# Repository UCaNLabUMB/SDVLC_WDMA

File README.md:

# SDVLC_WDMA
Board files and test software for an optical wireless communications wavelength division multiple access (WDMA) transmitter with compatibility for USRP software defined radio hardware.

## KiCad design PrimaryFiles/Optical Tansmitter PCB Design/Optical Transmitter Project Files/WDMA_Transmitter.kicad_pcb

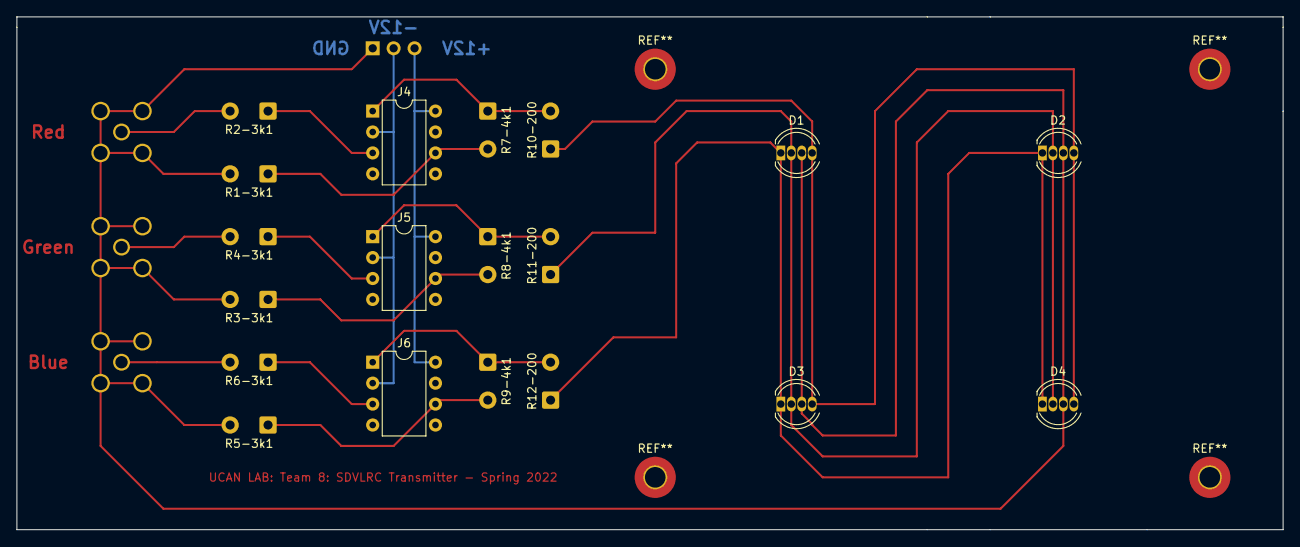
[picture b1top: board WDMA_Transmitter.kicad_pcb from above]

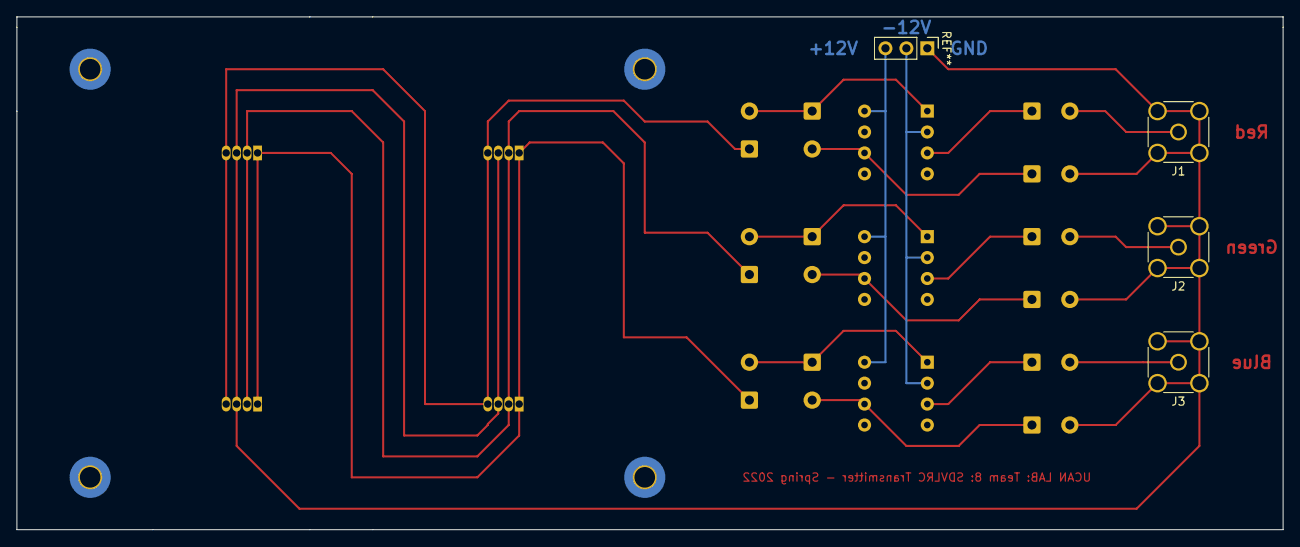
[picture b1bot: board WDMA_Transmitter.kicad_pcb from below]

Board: 2 copper layers, 153.7 x 62.2 mm, 22 parts (3 on the bottom side), 18 nets.

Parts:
D1, D2, D3, D4: LED_BGAR; LED_D5.0mm-4_RGB
J1, J2, J3: Conn_Coaxial; SMA_Wurth_60312002114503_Vertical
J4, J5, J6: Conn_02x04_Counter_Clockwise; DIP-8_W7.62mm
R1-3k1, R2-3k1, R3-3k1, R4-3k1, R5-3k1, R6-3k1: 3k; SolderWire-0.5sqmm_1x02_P4.6mm_D0.9mm_OD2.1mm
R7-4k1, R8-4k1, R9-4k1: 4k; SolderWire-0.5sqmm_1x02_P4.6mm_D0.9mm_OD2.1mm
R10-200, R11-200, R12-200: 200; SolderWire-0.5sqmm_1x02_P4.6mm_D0.9mm_OD2.1mm

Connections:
+12V: J4.8, J5.8, J6.8
-12V: J4.2, J5.2, J6.2
GND: D1.3, D2.3, D3.3, D4.3, J1.2, J2.2, J3.2, R1-3k1.2, R3-3k1.2, R5-3k1.2
unnamed: D1.1, D2.1, D3.1, D4.1, R12-200.1
unnamed: D1.2, D2.2, D3.2, D4.2, R11-200.1
unnamed: D1.4, D2.4, D3.4, D4.4, R10-200.1
unnamed: J1.1, R2-3k1.2
unnamed: J2.1, R4-3k1.2
unnamed: J3.1, R6-3k1.2
unnamed: J4.1, R7-4k1.1, R10-200.2
unnamed: J4.3, R2-3k1.1
unnamed: J4.6, R1-3k1.1, R7-4k1.2
unnamed: J5.1, R8-4k1.1, R11-200.2
unnamed: J5.3, R4-3k1.1
unnamed: J5.6, R3-3k1.1, R8-4k1.2
unnamed: J6.1, R9-4k1.1, R12-200.2
unnamed: J6.3, R6-3k1.1
unnamed: J6.6, R5-3k1.1, R9-4k1.2

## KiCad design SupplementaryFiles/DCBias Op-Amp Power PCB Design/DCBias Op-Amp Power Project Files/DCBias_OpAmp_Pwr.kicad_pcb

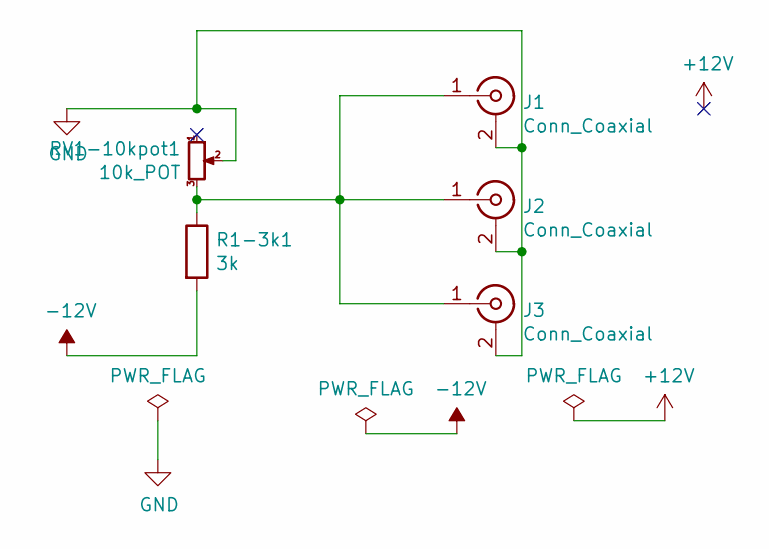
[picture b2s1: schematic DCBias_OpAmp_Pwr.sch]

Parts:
J1, J2, J3: Conn_Coaxial; SMA_Wurth_60312002114503_Vertical
R1-3k1: 3k; SolderWire-0.5sqmm_1x02_P4.6mm_D0.9mm_OD2.1mm
RV1-10kpot1: 10k_POT; Potentiometer_Bourns_3386P_Vertical

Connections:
-12V: R1-3k1.2
GND: J1.2 (Ext), J2.2 (Ext), J3.2 (Ext), RV1-10kpot1.2
unnamed: J1.1 (In), J2.1 (In), J3.1 (In), R1-3k1.1, RV1-10kpot1.3

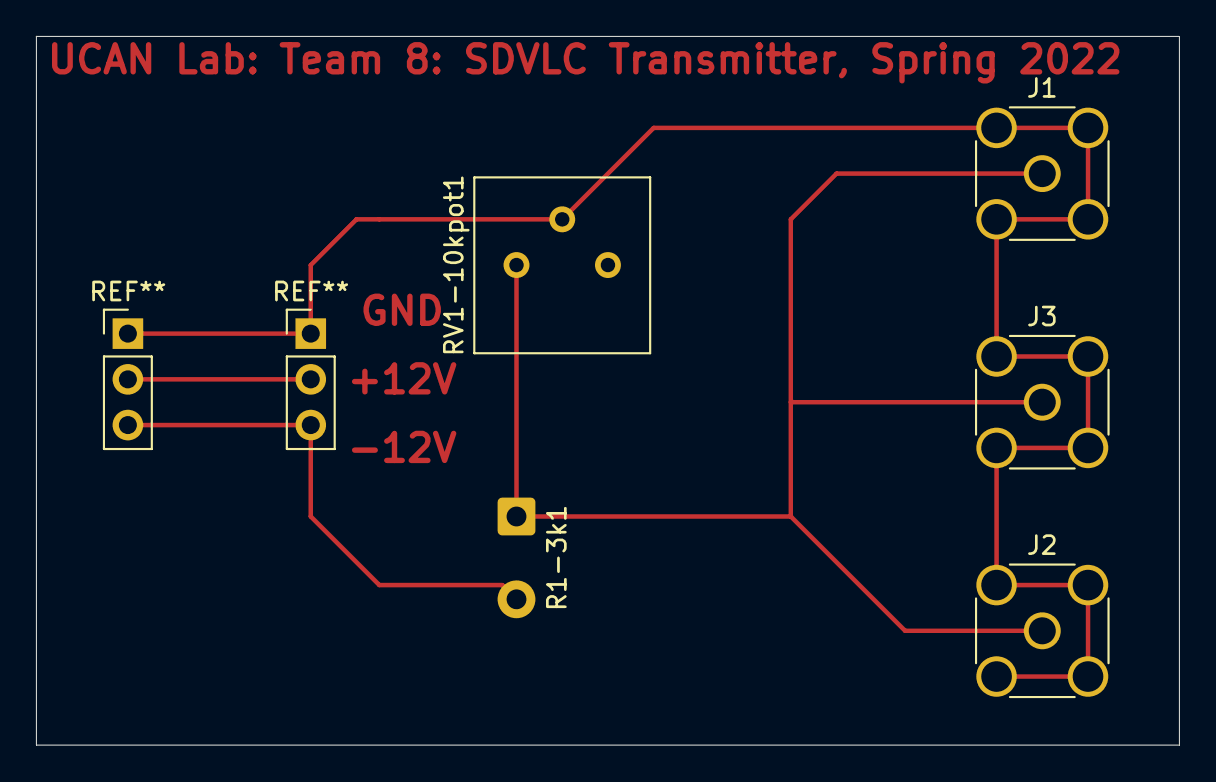
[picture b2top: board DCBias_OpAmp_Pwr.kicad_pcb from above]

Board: 2 copper layers, 63.5 x 39.4 mm, 5 parts (0 on the bottom side), 2 nets.

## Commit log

2022-08-17 Create Primary Files
2022-08-17 Create TransmitterPCB
2022-08-17 Create supplementary
2022-09-23 Updated File/Folder Names
2022-09-23 updated folder name
2022-09-23 Updated PCB Fabrication folder to zip
